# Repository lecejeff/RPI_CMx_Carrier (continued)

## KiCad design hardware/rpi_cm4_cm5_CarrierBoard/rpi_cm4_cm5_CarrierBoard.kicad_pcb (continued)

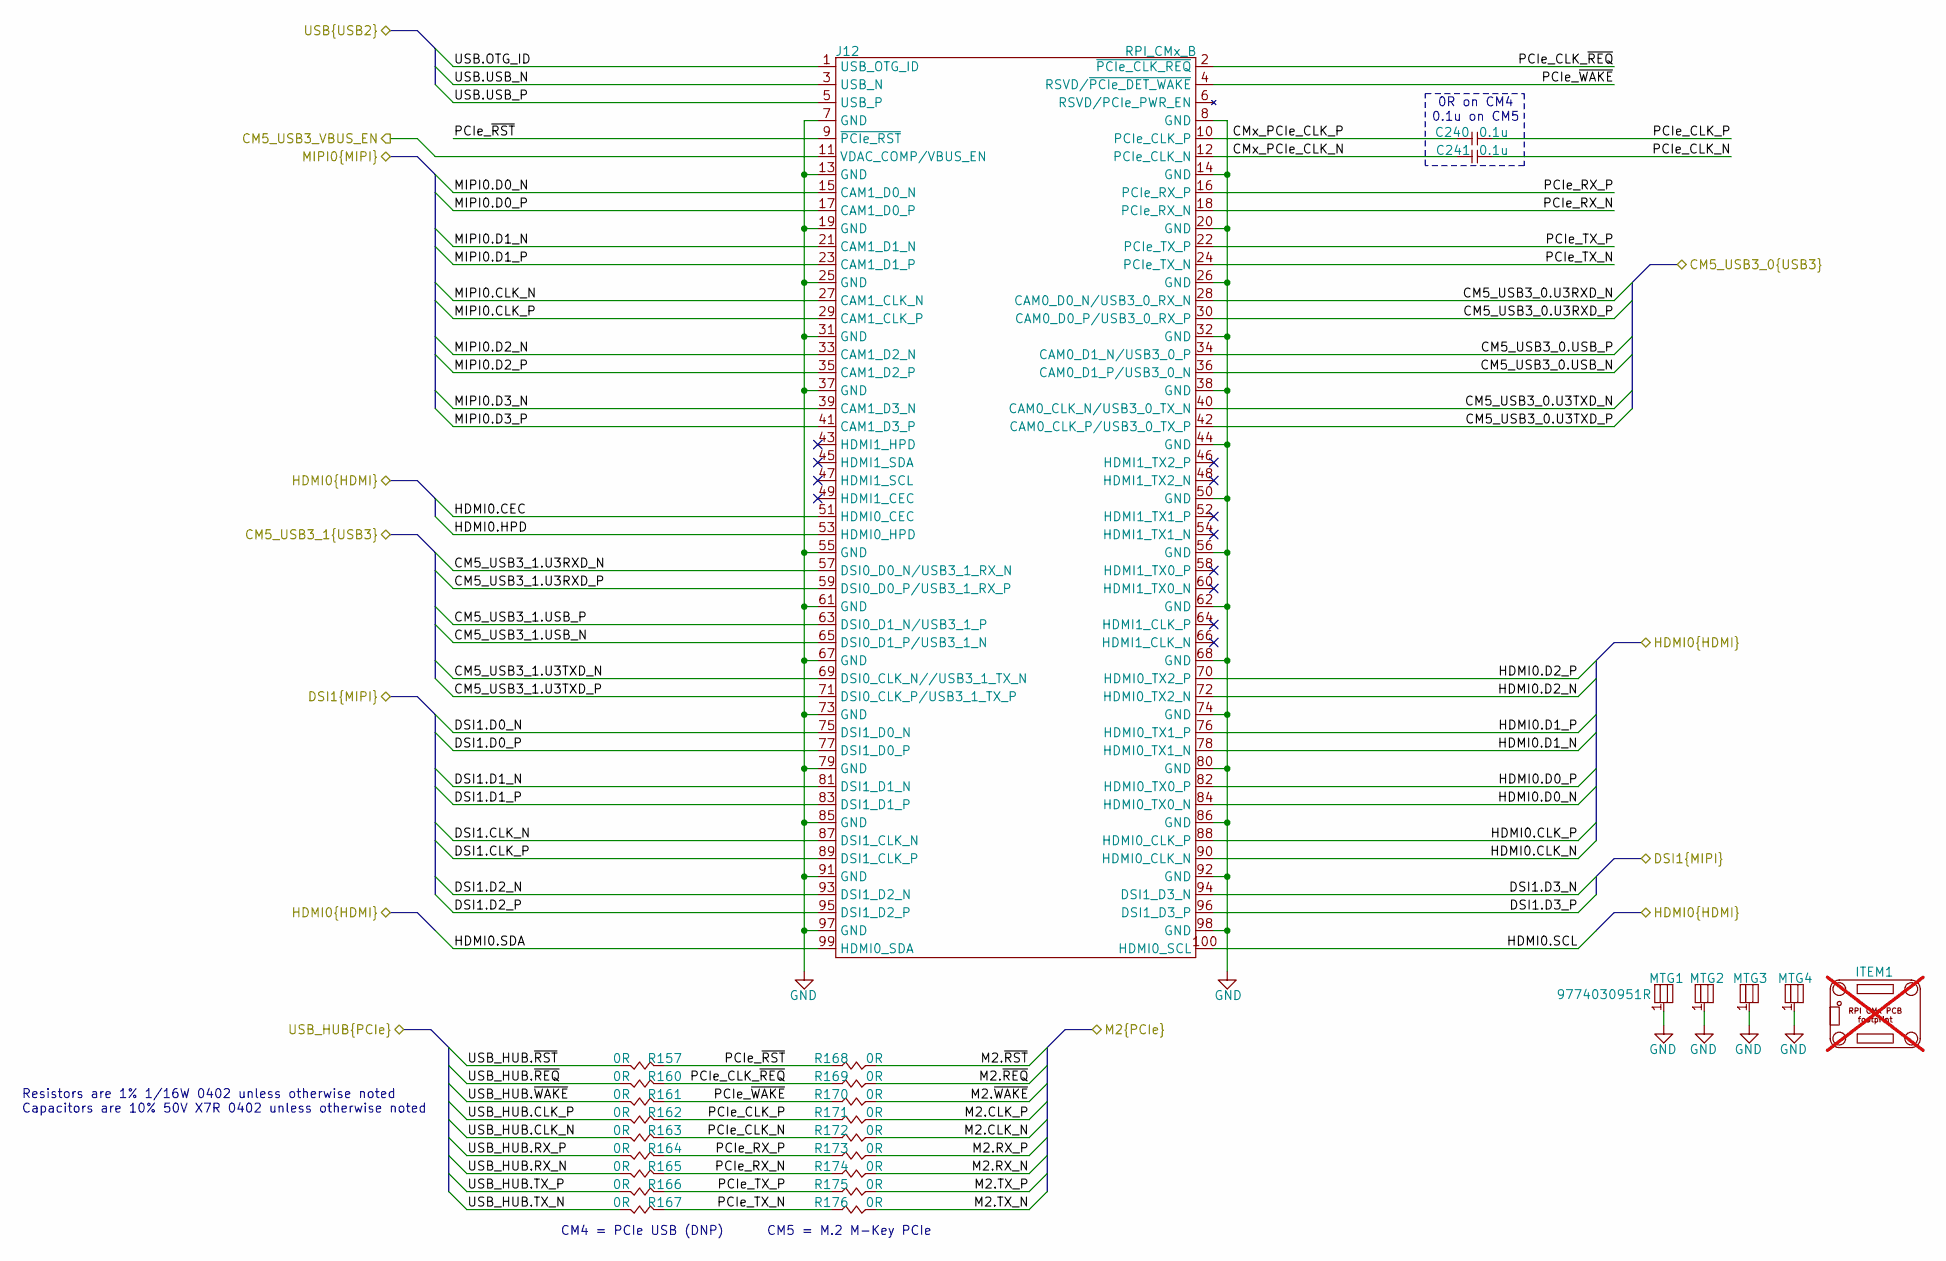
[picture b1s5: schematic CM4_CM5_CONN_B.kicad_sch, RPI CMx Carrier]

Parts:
C240, C241: 0.1u; CAP_NONPOL_0402; Tolerance ±10%; Voltage Rating 50V; Manufacturer Part Number GRM155R71H104KE14D
ITEM1: Raspberry PI CM4 and CM5 symbol; rPI_CM4_CM5; not fitted
J12: RPI_CMx_B; DF40HC(3.0)-100DS-0.4V; Current Rating 0.5A; Voltage Rating 150V; Manufacturer Part Number DF40HC(3.0)-100DS-0.4V(58)
MTG1, MTG2, MTG3, MTG4: 9774030951R; 9774030151R; Manufacturer Part Number 9774030951R
R157, R160, R161, R162, R163, R164, R165, R166, R167, R168, R169, R170, R171, R172, R173, R174, R175, R176: 0R; RES_0402; Tolerance 1%; Manufacturer Part Number RC0402FR-071KL

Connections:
/CM4_CM5_CONN_B/CMx_PCIe_CLK_N: C241.1, J12.12 (PCIe_CLK_N)
/CM4_CM5_CONN_B/CMx_PCIe_CLK_P: C240.1, J12.10 (PCIe_CLK_P)
/CM4_CM5_CONN_B/PCIe_CLK_N: C241.2, R163.1, R172.1
/CM4_CM5_CONN_B/PCIe_CLK_P: C240.2, R162.1, R171.1
/CM4_CM5_CONN_B/PCIe_CLK_~REQ: J12.2 (~PCIe_CLK_REQ), R160.1, R169.1
/CM4_CM5_CONN_B/PCIe_RX_N: J12.18 (PCIe_RX_N), R165.1, R174.1
/CM4_CM5_CONN_B/PCIe_RX_P: J12.16 (PCIe_RX_P), R164.1, R173.1
/CM4_CM5_CONN_B/PCIe_TX_N: J12.24 (PCIe_TX_N), R167.1, R176.1
/CM4_CM5_CONN_B/PCIe_TX_P: J12.22 (PCIe_TX_P), R166.1, R175.1
/CM4_CM5_CONN_B/PCIe_~RST: J12.9 (~PCIe_RST), R157.1, R168.1
/CM4_CM5_CONN_B/PCIe_~WAKE: J12.4 (RSVD/~PCIe_DET_WAKE), R161.1, R170.1
/CM5_USB3_0.U3RXD_N: J12.28 (CAM0_D0_N/USB3_0_RX_N); also elsewhere on the board
/CM5_USB3_0.U3RXD_P: J12.30 (CAM0_D0_P/USB3_0_RX_P); also elsewhere on the board
/CM5_USB3_0.U3TXD_N: J12.40 (CAM0_CLK_N/USB3_0_TX_N); also elsewhere on the board
/CM5_USB3_0.U3TXD_P: J12.42 (CAM0_CLK_P/USB3_0_TX_P); also elsewhere on the board
/CM5_USB3_0.USB_N: J12.36 (CAM0_D1_P/USB3_0_N); also elsewhere on the board
/CM5_USB3_0.USB_P: J12.34 (CAM0_D1_N/USB3_0_P); also elsewhere on the board
/CM5_USB3_1.U3RXD_N: J12.57 (DSI0_D0_N/USB3_1_RX_N); also elsewhere on the board
/CM5_USB3_1.U3RXD_P: J12.59 (DSI0_D0_P/USB3_1_RX_P); also elsewhere on the board
/CM5_USB3_1.U3TXD_N: J12.69 (DSI0_CLK_N//USB3_1_TX_N); also elsewhere on the board
/CM5_USB3_1.U3TXD_P: J12.71 (DSI0_CLK_P/USB3_1_TX_P); also elsewhere on the board
/CM5_USB3_1.USB_N: J12.65 (DSI0_D1_P/USB3_1_N); also elsewhere on the board
/CM5_USB3_1.USB_P: J12.63 (DSI0_D1_N/USB3_1_P); also elsewhere on the board
/DSI1.CLK_N: J12.87 (DSI1_CLK_N); also elsewhere on the board
/DSI1.CLK_P: J12.89 (DSI1_CLK_P); also elsewhere on the board
/DSI1.D0_N: J12.75 (DSI1_D0_N); also elsewhere on the board
/DSI1.D0_P: J12.77 (DSI1_D0_P); also elsewhere on the board
/DSI1.D1_N: J12.81 (DSI1_D1_N); also elsewhere on the board
/DSI1.D1_P: J12.83 (DSI1_D1_P); also elsewhere on the board
/DSI1.D2_N: J12.93 (DSI1_D2_N); also elsewhere on the board
/DSI1.D2_P: J12.95 (DSI1_D2_P); also elsewhere on the board
/DSI1.D3_N: J12.94 (DSI1_D3_N); also elsewhere on the board
/DSI1.D3_P: J12.96 (DSI1_D3_P); also elsewhere on the board
/HDMI0.CEC: J12.51 (HDMI0_CEC); also elsewhere on the board
/HDMI0.CLK_N: J12.90 (HDMI0_CLK_N); also elsewhere on the board
/HDMI0.CLK_P: J12.88 (HDMI0_CLK_P); also elsewhere on the board
/HDMI0.D0_N: J12.84 (HDMI0_TX0_N); also elsewhere on the board
/HDMI0.D0_P: J12.82 (HDMI0_TX0_P); also elsewhere on the board
/HDMI0.D1_N: J12.78 (HDMI0_TX1_N); also elsewhere on the board
/HDMI0.D1_P: J12.76 (HDMI0_TX1_P); also elsewhere on the board
/HDMI0.D2_N: J12.72 (HDMI0_TX2_N); also elsewhere on the board
/HDMI0.D2_P: J12.70 (HDMI0_TX2_P); also elsewhere on the board
/HDMI0.HPD: J12.53 (HDMI0_HPD); also elsewhere on the board
/HDMI0.SCL: J12.100 (HDMI0_SCL); also elsewhere on the board
/HDMI0.SDA: J12.99 (HDMI0_SDA); also elsewhere on the board
/M2.CLK_N: R172.2; also elsewhere on the board
/M2.CLK_P: R171.2; also elsewhere on the board
/M2.RX_N: R174.2; also elsewhere on the board
/M2.RX_P: R173.2; also elsewhere on the board
/M2.TX_N: R176.2; also elsewhere on the board
/M2.TX_P: R175.2; also elsewhere on the board
/M2.~REQ: R169.2; also elsewhere on the board
/M2.~RST: R168.2; also elsewhere on the board
/M2.~WAKE: R170.2; also elsewhere on the board
/MIPI0.CLK_N: J12.27 (CAM1_CLK_N); also elsewhere on the board
/MIPI0.CLK_P: J12.29 (CAM1_CLK_P); also elsewhere on the board
/MIPI0.D0_N: J12.15 (CAM1_D0_N); also elsewhere on the board
/MIPI0.D0_P: J12.17 (CAM1_D0_P); also elsewhere on the board
/MIPI0.D1_N: J12.21 (CAM1_D1_N); also elsewhere on the board
/MIPI0.D1_P: J12.23 (CAM1_D1_P); also elsewhere on the board
/MIPI0.D2_N: J12.33 (CAM1_D2_N); also elsewhere on the board
/MIPI0.D2_P: J12.35 (CAM1_D2_P); also elsewhere on the board
/MIPI0.D3_N: J12.39 (CAM1_D3_N); also elsewhere on the board
/MIPI0.D3_P: J12.41 (CAM1_D3_P); also elsewhere on the board
/USB.OTG_ID: J12.1 (USB_OTG_ID); also elsewhere on the board
/USB.USB_N: J12.3 (USB_N); also elsewhere on the board
/USB.USB_P: J12.5 (USB_P); also elsewhere on the board
/USB_3/CM5_USB3_VBUS_EN: J12.11 (VDAC_COMP/VBUS_EN); also elsewhere on the board
/USB_HUB.CLK_N: R163.2; also elsewhere on the board
/USB_HUB.CLK_P: R162.2; also elsewhere on the board
/USB_HUB.RX_N: R165.2; also elsewhere on the board
/USB_HUB.RX_P: R164.2; also elsewhere on the board
/USB_HUB.TX_N: R167.2; also elsewhere on the board
/USB_HUB.TX_P: R166.2; also elsewhere on the board
/USB_HUB.~REQ: R160.2; also elsewhere on the board
/USB_HUB.~RST: R157.2; also elsewhere on the board
/USB_HUB.~WAKE: R161.2; also elsewhere on the board
GND: J12.7 (GND), J12.8 (GND), J12.13 (GND), J12.14 (GND), J12.19 (GND), J12.20 (GND), J12.25 (GND), J12.26 (GND), J12.31 (GND), J12.32 (GND), J12.37 (GND), J12.38 (GND), J12.44 (GND), J12.50 (GND), J12.55 (GND), J12.56 (GND), J12.61 (GND), J12.62 (GND), J12.67 (GND), J12.68 (GND), J12.73 (GND), J12.74 (GND), J12.79 (GND), J12.80 (GND), J12.85 (GND), J12.86 (GND), J12.91 (GND), J12.92 (GND), J12.97 (GND), J12.98 (GND), MTG1.1, MTG2.1, MTG3.1, MTG4.1; also elsewhere on the board

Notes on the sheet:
Resistors are 1% 1/16W 0402 unless otherwise noted Capacitors are 10% 50V X7R 0402 unless otherwise noted
0R on CM4 0.1u on CM5
CM4 = PCIe USB (DNP)
CM5 = M.2 M-Key PCIe

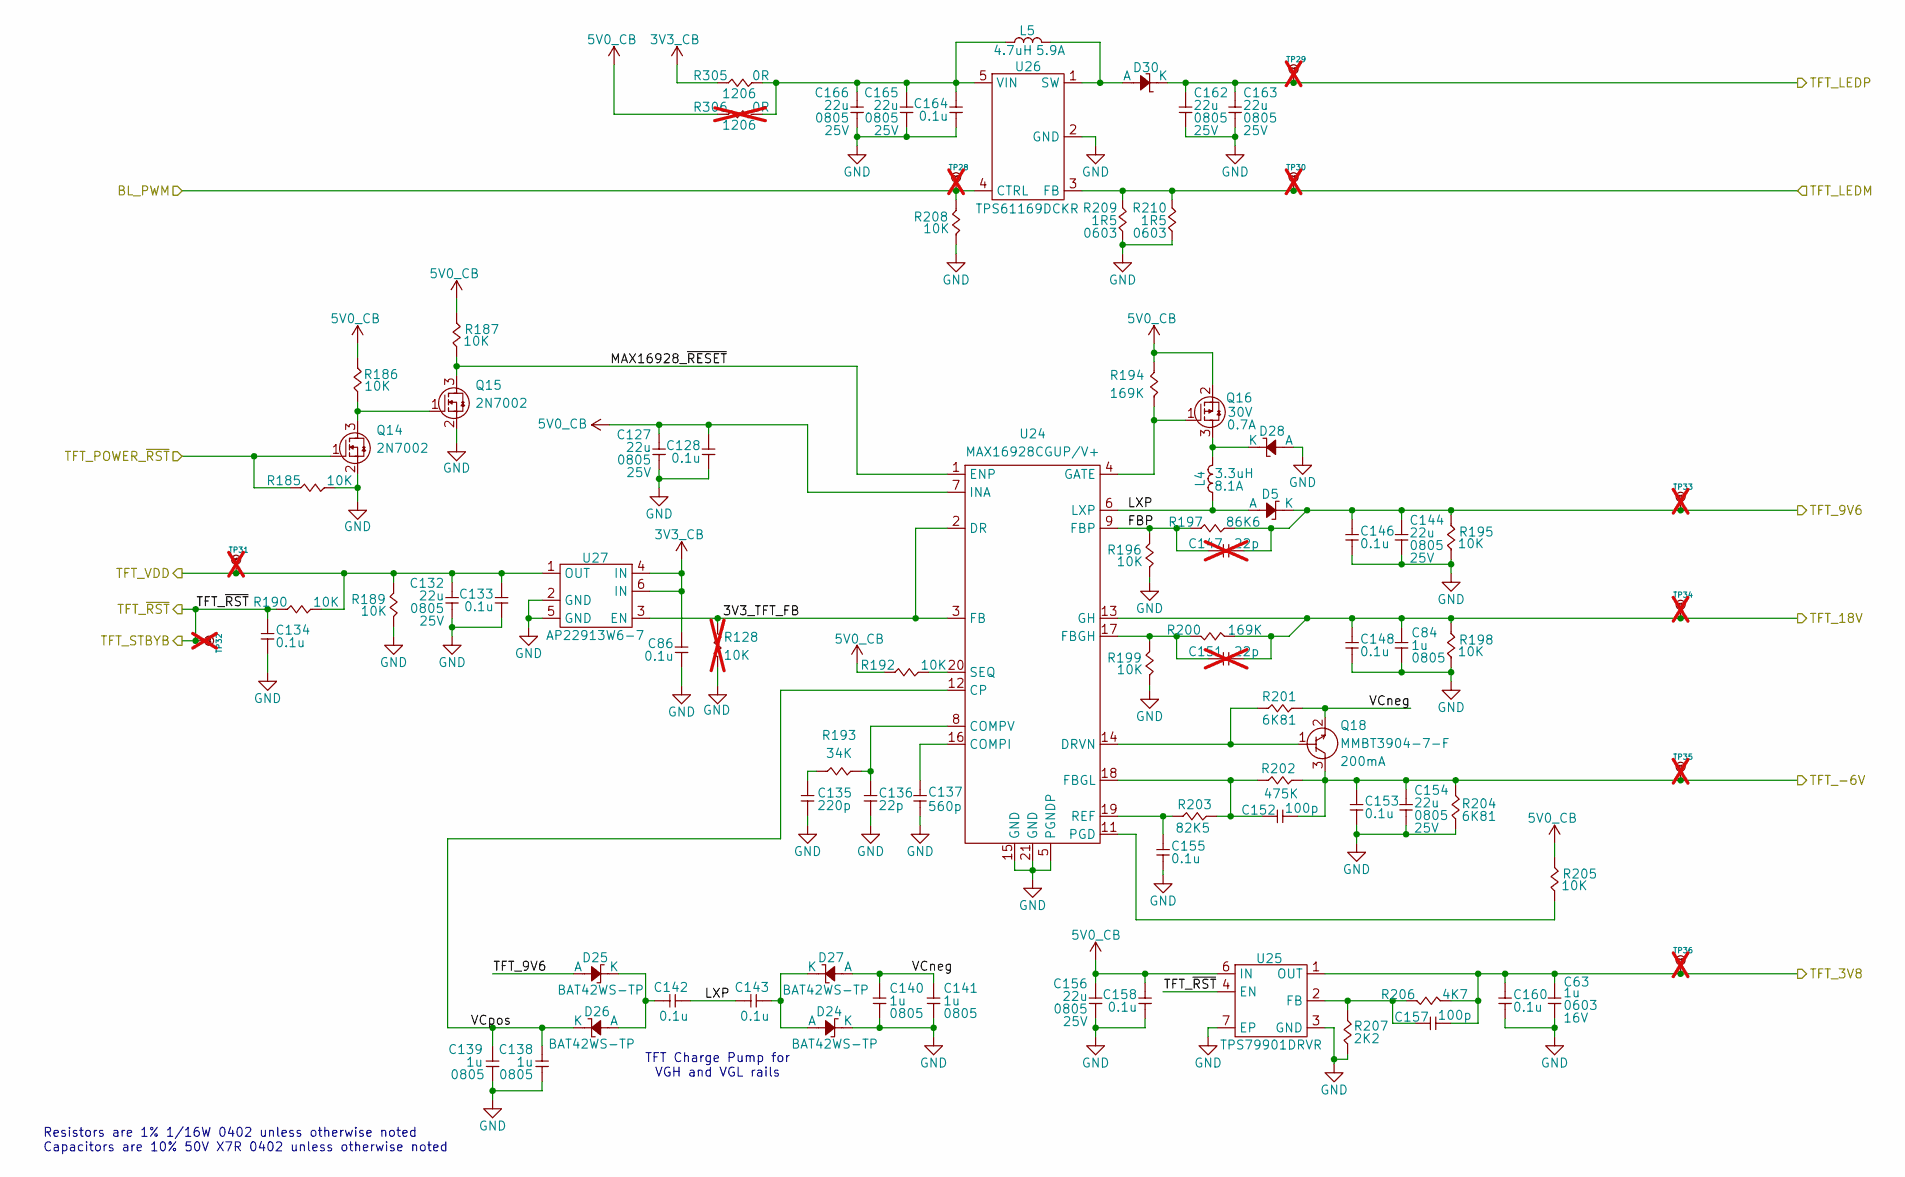
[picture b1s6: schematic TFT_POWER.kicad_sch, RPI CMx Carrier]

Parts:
C63: 1u; CAP_NONPOL_0603; Tolerance ±10%; Voltage Rating 16V; Manufacturer Part Number CC0603KRX7R7BB105
C84, C138, C139, C140, C141: 1u; CAP_NONPOL_0805; Tolerance ±10%; Voltage Rating 50V; Manufacturer Part Number CC0805KKX7R9BB105
C86, C128, C133, C134, C142, C143, C146, C148, C153, C155, C158, C160, C164: 0.1u; CAP_NONPOL_0402; Tolerance ±10%; Voltage Rating 50V; Manufacturer Part Number GRM155R71H104KE14D
C127, C132, C144, C154, C156, C162, C163, C165, C166: 22u; CAP_NONPOL_0805; Tolerance ±20%; Voltage Rating 25V; Manufacturer Part Number CL21A226MAYNNNE
C135: 220p; CAP_NONPOL_0402; Tolerance ±5%; Voltage Rating 50V; Manufacturer Part Number CL05C221JB5NNNC
C136: 22p; CAP_NONPOL_0402; Tolerance ±10%; Voltage Rating 50V; Manufacturer Part Number C0402C220K5GACTU
C137: 560p; CAP_NONPOL_0402; Tolerance ±5%; Voltage Rating 50V; Manufacturer Part Number GRM1555C1H561JA01D
C147, C151: 22p; CAP_NONPOL_0402; Tolerance ±10%; Voltage Rating 50V; Manufacturer Part Number C0402C220K5GACTU; not fitted
C152, C157: 100p; CAP_NONPOL_0402; Tolerance ±5%; Voltage Rating 50V; Manufacturer Part Number CC0402JRNPO9BN101
D5, D24, D25, D26, D27, D28: BAT42WS-TP; SOD-323; Tolerance NA; Manufacturer Part Number BAT42WS-TP
D30: SK34A-LTP; DO-214AC; Tolerance NA; Manufacturer Part Number SK34A-LTP
L4: PA5003.332NLT; PA5003; Tolerance ±20%; Manufacturer Part Number PA5003.332NLT
L5: PA5003.472NLT; PA5003; Tolerance ±20%; Manufacturer Part Number PA5003.472NLT
Q14, Q15: 2N7002; SOT-23-3; Manufacturer Part Number 2N7002-7-F
Q16: DMP3030SN-7; SOT-23-3; Manufacturer Part Number DMP3030SN-7
Q18: MMBT3904-7-F; SOT-23-3; Manufacturer Part Number MMBT3904-7-F
R128: 10K; RES_0402; Tolerance 1%; Manufacturer Part Number RC0402FR-0710KL; not fitted
R185, R186, R187, R189, R190, R192, R195, R196, R198, R199, R205, R208: 10K; RES_0402; Tolerance 1%; Manufacturer Part Number RC0402FR-0710KL
R193: 34K; RES_0402; Tolerance 1%; Manufacturer Part Number RC0402FR-1334KL
R194, R200: 169K; RES_0402; Tolerance 1%; Manufacturer Part Number RC0402FR-07169KL
R197: 86K6; RES_0402; Tolerance 1%; Manufacturer Part Number AC0402FR-0786K6L
R201, R204: 6K81; RES_0402; Tolerance 1%; Manufacturer Part Number RC0402FR-076K81L
R202: 475K; RES_0402; Tolerance 1%; Manufacturer Part Number RC0402FR-07475KL
R203: 82K5; RES_0402; Tolerance 1%; Manufacturer Part Number RC0402FR-0782K5L
R206: 4K7; RES_0402; Tolerance 1%; Manufacturer Part Number RC0402FR-074K7L
R207: 2K2; RES_0402; Tolerance 1%; Manufacturer Part Number RC0402FR-072K2P
R209, R210: 1R5; RES_0603; Tolerance 1%; Manufacturer Part Number RC0603FR-131R5L
R305: 0R; RES_1206; Tolerance 1%; Manufacturer Part Number RC1206JR-070RL
R306: 0R; RES_1206; Tolerance 1%; Manufacturer Part Number RC1206JR-070RL; not fitted
TP28, TP29, TP30, TP31, TP32, TP33, TP34, TP35, TP36: 28 mils; SMT_TP_28_MILS; Manufacturer Part Number NA; not fitted
U24: MAX16928CGUP/V+; TSSOP-20-EP; Input Voltage (Min) 3V; Input Voltage (Max) 5.5V; Manufacturer Part Number MAX16928CGUP/V+
U25: TPS79901DRVR; WSON-6-EP; Input Voltage (Min) 2.7V; Input Voltage (Max) 6.5V; Manufacturer Part Number TPS79901DRVR
U26: TPS61169DCKR; SC-70-5; Input Voltage (Min) 2.7V; Input Voltage (Max) 5.5V; Manufacturer Part Number TPS61169DCKR
U27: AP22913W6-7; SOT-23-6; Load Voltage 1.5V ~ 5.5V; Manufacturer Part Number AP22913W6-7

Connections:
3V3_CB: C86.2, R305.1, U27.4 (IN), U27.6 (IN); also elsewhere on the board
5V0_CB: C127.2, C128.2, C156.2, C158.2, Q16.2 (S), R186.2, R187.2, R192.2, R194.2, R205.2, R306.1, U24.7 (INA), U25.6 (IN); also elsewhere on the board
/CM4_CM5_CONN_A/PWM_0: R208.2, TP28.1, U26.4 (CTRL); also elsewhere on the board
/TFT_CONN/TFT_LEDM: R209.2, R210.2, TP30.1, U26.3 (FB); also elsewhere on the board
/TFT_CONN/TFT_LEDP: C162.2, C163.2, D30.1 (K), TP29.1; also elsewhere on the board
/TFT_CONN/TFT_VCOM: C63.2, C157.2, C160.2, R206.1, TP36.1, U25.1 (OUT); also elsewhere on the board
/TFT_CONN/TFT_VDD: C132.2, C133.2, R189.2, R190.1, TP31.1, U27.1 (OUT); also elsewhere on the board
/TFT_CONN/TFT_VGH: C84.2, C148.2, C151.1, R198.2, R200.1, TP34.1, U24.13 (GH); also elsewhere on the board
/TFT_CONN/TFT_VGL: C152.2, C153.2, C154.2, Q18.3 (C), R202.2, R204.2, TP35.1; also elsewhere on the board
/TFT_POWER/3V3_TFT_FB: R128.2, U24.2 (DR), U24.3 (FB), U27.3 (EN)
/TFT_POWER/FBP: C147.2, R196.2, R197.1, U24.9 (FBP)
/TFT_POWER/LXP: C142.1, C143.2, D5.2 (A), L4.1, U24.6 (LXP)
/TFT_POWER/MAX16928_~RESET: Q15.3 (D), R187.1, U24.1 (ENP)
/TFT_POWER/TFT_9V6: C144.2, C146.2, C147.1, D5.1 (K), D25.2 (A), R195.2, R197.2, TP33.1; also elsewhere on the board
/TFT_POWER/TFT_~RST: C134.2, R190.2, TP32.1, U25.4 (EN); also elsewhere on the board
/TFT_POWER/VCneg: C140.2, C141.2, D27.2 (A), Q18.2 (E), R201.2
/TFT_POWER/VCpos: C138.2, C139.2, D26.1 (K), U24.12 (CP)
/TFT_POWER_~RST: Q14.1 (G), R185.2; also elsewhere on the board
GND: C63.1, C84.1, C86.1, C127.1, C128.1, C132.1, C133.1, C134.1, C135.1, C136.1, C137.1, C138.1, C139.1, C140.1, C141.1, C144.1, C146.1, C148.1, C153.1, C154.1, C155.1, C156.1, C158.1, C160.1, C162.1, C163.1, C164.1, C165.1, C166.1, D24.1 (K), D28.2 (A), Q14.2 (S), Q15.2 (S), R128.1, R185.1, R189.1, R195.1, R196.1, R198.1, R199.1, R204.1, R207.1, R208.1, R209.1, R210.1, U24.5 (PGNDP), U24.15 (GND), U24.21 (GND), U25.3 (GND), U25.7 (EP), U26.2 (GND), U27.2 (GND), U27.5 (GND); also elsewhere on the board
unnamed: C135.2, R193.1
unnamed: C143.1, D24.2 (A), D27.1 (K)
unnamed: C142.2, D25.1 (K), D26.2 (A)
unnamed: D28.1 (K), L4.2, Q16.3 (D)
unnamed: D30.2 (A), L5.2, U26.1 (SW)
unnamed: Q14.3 (D), Q15.1 (G), R186.1
unnamed: Q16.1 (G), R194.1, U24.4 (GATE)
unnamed: Q18.1 (B), R201.1, U24.14 (DRVN)
unnamed: C137.2, U24.16 (COMPI)
unnamed: C136.2, R193.2, U24.8 (COMPV)
unnamed: C151.2, R199.2, R200.2, U24.17 (FBGH)
unnamed: C152.1, R202.1, R203.2, U24.18 (FBGL)
unnamed: R205.1, U24.11 (PGD)
unnamed: C155.2, R203.1, U24.19 (REF)
unnamed: R192.1, U24.20 (SEQ)
unnamed: C157.1, R206.2, R207.2, U25.2 (FB)
unnamed: C164.2, C165.2, C166.2, L5.1, R305.2, R306.2, U26.5 (VIN)

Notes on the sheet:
Resistors are 1% 1/16W 0402 unless otherwise noted Capacitors are 10% 50V X7R 0402 unless otherwise noted
TFT Charge Pump for VGH and VGL rails

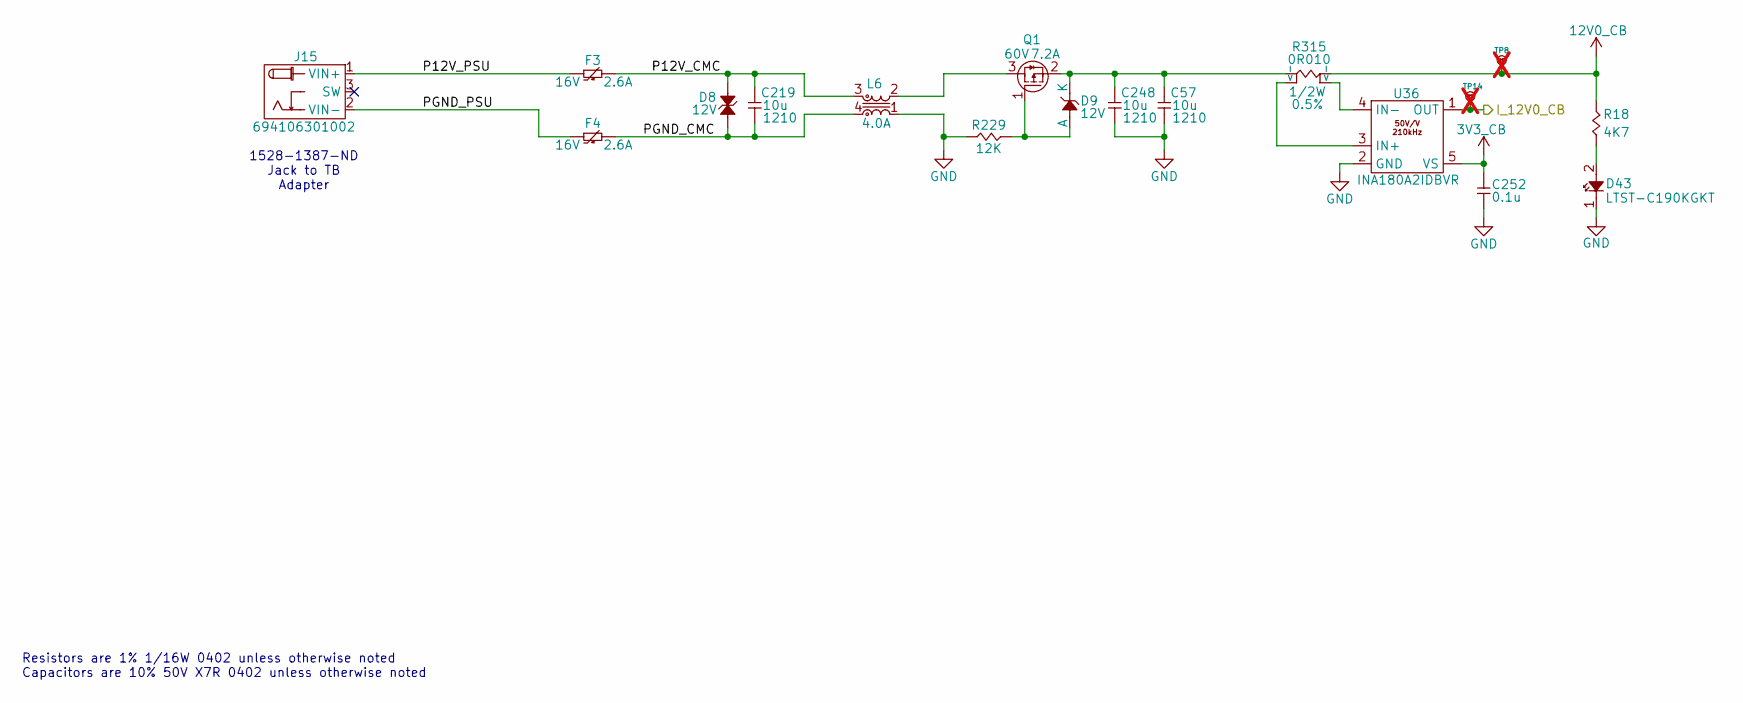
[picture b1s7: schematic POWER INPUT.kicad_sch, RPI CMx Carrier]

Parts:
C57, C219, C248: 10u; CAP_NONPOL_1210; Tolerance ±10%; Voltage Rating 50V; Manufacturer Part Number C3225X7R1H106K250AC
C252: 0.1u; CAP_NONPOL_0402; Tolerance ±10%; Voltage Rating 50V; Manufacturer Part Number GRM155R71H104KE14D
D8: SMAJ12CA; DO-214AC; Manufacturer Part Number SMAJ12CA
D9: MMSZ5242B-TP; SOD-123; Tolerance ±5%; Manufacturer Part Number MMSZ5242B-TP
D43: LTST-C190KGKT; LED_0603; Tolerance NA; Manufacturer Part Number LTST-C190KGKT
F3, F4: MINISMDC260F/16-2; PTC_1812; Voltage 16V; Manufacturer Part Number MINISMDC260F/16-2
J15: 694106301002; Current Rating 5A; Voltage Rating 24V; Manufacturer Part Number 694106301002
L6: CM7060P701R-10; CM7060; Tolerance NA; Manufacturer Part Number CM7060P701R-10
Q1: DMPH6050SK3-13; TO-252-3; Manufacturer Part Number DMPH6050SK3-13
R18: 4K7; RES_0402; Tolerance 1%; Manufacturer Part Number RC0402FR-074K7L
R229: 12K; RES_0402; Tolerance 1%; Manufacturer Part Number RC0402FR-1312KL
R315: 0R010; RES_SENSE_1206; Tolerance 0.5%; Manufacturer Part Number LVK12R010DER
TP8, TP14: 28 mils; SMT_TP_28_MILS; Manufacturer Part Number NA; not fitted
U36: INA180A2IDBVR; SOT-23-5; Offset Voltage 100uV; Supply Voltage 2.7V ~ 5.5V; Manufacturer Part Number INA180A2IDBVR

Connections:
3V3_CB: C252.2, U36.5 (VS); also elsewhere on the board
12V0_CB: R18.2, R315.4 (I), TP8.1; also elsewhere on the board
/PIC32AK1216/I_12V0_CB: TP14.1, U36.1 (OUT); also elsewhere on the board
/POWER INPUT/P12V_CMC: C219.2, D8.2, F3.2, L6.3
/POWER INPUT/P12V_PSU: F3.1, J15.1 (VIN+)
/POWER INPUT/PGND_CMC: C219.1, D8.1, F4.2, L6.4
/POWER INPUT/PGND_PSU: F4.1, J15.2 (VIN-)
GND: C57.1, C248.1, C252.1, D43.1 (K), L6.1, R229.1, U36.2 (GND); also elsewhere on the board
unnamed: D9.2 (A), Q1.1 (G), R229.2
unnamed: C57.2, C248.2, D9.1 (K), Q1.2 (S), R315.1 (I)
unnamed: D43.2 (A), R18.1
unnamed: L6.2, Q1.3 (D)
unnamed: R315.2 (V), U36.3 (IN+)
unnamed: R315.3 (V), U36.4 (IN-)

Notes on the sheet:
1528-1387-ND Jack to TB Adapter
Resistors are 1% 1/16W 0402 unless otherwise noted Capacitors are 10% 50V X7R 0402 unless otherwise noted

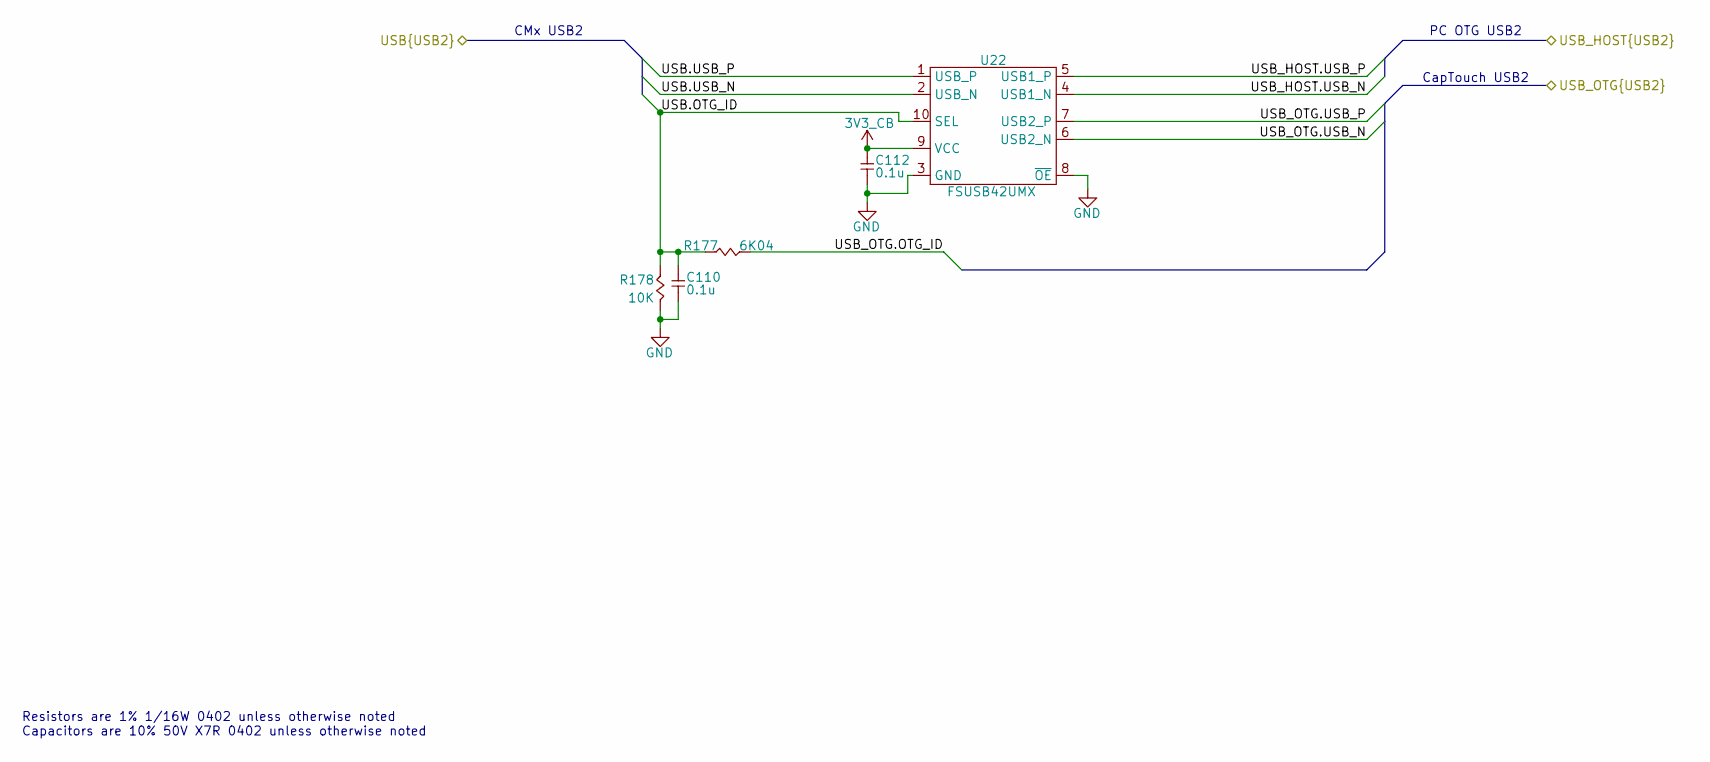
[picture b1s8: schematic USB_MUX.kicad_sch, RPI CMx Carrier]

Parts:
C110, C112: 0.1u; CAP_NONPOL_0402; Tolerance ±10%; Voltage Rating 50V; Manufacturer Part Number GRM155R71H104KE14D
R177: 6K04; RES_0402; Tolerance 1%; Manufacturer Part Number RC0402FR-076K04P
R178: 10K; RES_0402; Tolerance 1%; Manufacturer Part Number RC0402FR-0710KL
U22: FSUSB42UMX; 10-UMLP; Supply Voltage 2.4V ~ 4.4V; Manufacturer Part Number FSUSB42UMX

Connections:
3V3_CB: C112.2, U22.9 (VCC); also elsewhere on the board
/TFT_CONN/USB_HOST.USB_N: U22.4 (USB1_N); also elsewhere on the board
/TFT_CONN/USB_HOST.USB_P: U22.5 (USB1_P); also elsewhere on the board
/USB.OTG_ID: C110.2, R177.1, R178.2, U22.10 (SEL); also elsewhere on the board
/USB.USB_N: U22.2 (USB_N); also elsewhere on the board
/USB.USB_P: U22.1 (USB_P); also elsewhere on the board
/USB_OTG.OTG_ID: R177.2; also elsewhere on the board
/USB_OTG.USB_N: U22.6 (USB2_N); also elsewhere on the board
/USB_OTG.USB_P: U22.7 (USB2_P); also elsewhere on the board
GND: C110.1, C112.1, R178.1, U22.3 (GND), U22.8 (~OE); also elsewhere on the board

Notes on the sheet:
CapTouch USB2
Resistors are 1% 1/16W 0402 unless otherwise noted Capacitors are 10% 50V X7R 0402 unless otherwise noted
CMx USB2
PC OTG USB2

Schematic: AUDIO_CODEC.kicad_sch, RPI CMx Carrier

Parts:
C203, C204, C208, C211, C212, C214, C217: 0.1u; CAP_NONPOL_0402; Tolerance ±10%; Voltage Rating 50V; Manufacturer Part Number GRM155R71H104KE14D
C205: 1u; CAP_NONPOL_0805; Tolerance ±10%; Voltage Rating 50V; Manufacturer Part Number CC0805KKX7R9BB105; not fitted
C206, C207, C209, C210, C213, C215: 1u; CAP_NONPOL_0805; Tolerance ±10%; Voltage Rating 50V; Manufacturer Part Number CC0805KKX7R9BB105
C216: 10u; CAP_NONPOL_0805; Tolerance ±10%; Voltage Rating 16V; Manufacturer Part Number CL21A106KOQNNNE
D44, D45: D1213A-02SOL-7; SOT-23-3; Manufacturer Part Number D1213A-02SOL-7
J13, J14: SJ-3523-SMT-TR; SJ-352X-SMT; Current Rating 1A; Voltage Rating 12V; Manufacturer Part Number SJ-3523-SMT-TR
R16, R17, R279: 10K; RES_0402; Tolerance 1%; Manufacturer Part Number RC0402FR-0710KL
R275: 2K2; RES_0402; Tolerance 1%; Manufacturer Part Number RC0402FR-072K2P; not fitted
R276, R277: 22R; RES_0402; Tolerance 1%; Manufacturer Part Number RC0402FR-0722RL
TP37, TP38, TP39, TP40: 28 mils; SMT_TP_28_MILS; Manufacturer Part Number NA; not fitted
U2: ECS-2016MVQ-120-BP-TR; 4-SMD_2mmx1_6mm; Tolerance ±50ppm; Supply Voltage 3.3V; Manufacturer Part Number ECS-2016MVQ-120-BP-TR
U33: SGTL5000XNBA3R2; 32-HPQFN; Supply Voltage 1.1V ~ 3.6V; Manufacturer Part Number SGTL5000XNBA3R2
X1: CMM-3729AT-42308-TR; Manufacturer Part Number CMM-3729AT-42308-TR

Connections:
1V8_CB: C211.2, C213.2, U33.30 (VDDD); also elsewhere on the board
3V3_CB: C203.2, C212.2, C214.2, C215.2, C216.2, C217.2, U2.4 (VDD), U33.5 (VDDA), U33.20 (VDDIO), X1.1 (VDD); also elsewhere on the board
/AUDIO_CODEC/CODEC_CLK_12MHz: R277.2, U33.21 (MCLK)
/AUDIO_CODEC/HEADPHONE_L: D45.1, J14.2 (L), U33.6 (HP_L)
/AUDIO_CODEC/HEADPHONE_R: D45.2 (A), J14.3 (R), U33.2 (HP_R)
/AUDIO_CODEC/HEADPHONE_VGND: D45.3 (GND), J14.1 (SLV), U33.4 (HP_VGND)
/AUDIO_CODEC/LINE_IN_L: C206.2, R17.2
/AUDIO_CODEC/LINE_IN_R: C207.2, R16.2
/AUDIO_CODEC/LINE_OUT_L: C209.1, D44.2 (A), J13.2 (L)
/AUDIO_CODEC/LINE_OUT_R: C210.1, D44.1, J13.3 (R)
/AUDIO_CODEC/MIC_IN: C204.1, U33.15 (MIC)
/CODEC_~RST: R279.2, U2.1 (EN); also elsewhere on the board
/I2C3.I2C_SCL: U33.29 (CTRL_CLK); also elsewhere on the board
/I2C3.I2C_SDA: U33.27 (CTRL_DATA); also elsewhere on the board
/I2S_COFS: TP39.1, U33.23 (LRCLK); also elsewhere on the board
/I2S_DIN: R276.2, TP38.1; also elsewhere on the board
/I2S_DOUT: TP37.1, U33.26 (DIN); also elsewhere on the board
/I2S_SCLK: TP40.1, U33.24 (SCLK); also elsewhere on the board
GND: C203.1, C205.2, C208.1, C211.1, C212.1, C213.1, C214.1, C215.1, C216.1, C217.1, D44.3 (GND), J13.1 (SLV), R16.1, R17.1, R279.1, U2.2 (GND), U33.1 (GND), U33.3 (GND), U33.7 (AGND), U33.31 (CTRL_ADR0_CS), U33.32 (MODE), U33.33 (GND), X1.2 (GND), X1.3 (GND); also elsewhere on the board
unnamed: R277.1, U2.3 (OUT)
unnamed: R276.1, U33.25 (DOUT)
unnamed: C206.1, U33.14 (LINE_IN_L)
unnamed: C207.1, U33.13 (LINE_IN_R)
unnamed: C209.2, U33.12 (LINE_OUT_L)
unnamed: C210.2, U33.11 (LINE_OUT_R)
unnamed: C205.1, R275.2, U33.16 (MIC_BIAS)
unnamed: C208.2, U33.10 (VAG)
unnamed: C204.2, R275.1, X1.4 (OUT)

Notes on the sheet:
Resistors are 1% 1/16W 0402 unless otherwise noted Capacitors are 10% 50V X7R 0402 unless otherwise noted
I2C3 PU Pop'd at DSI bridge

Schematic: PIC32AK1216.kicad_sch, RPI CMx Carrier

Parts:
C1, C42, C44, C46, C47, C50, C52, C53, C54, C55, C75, C85, C253: 0.1u; CAP_NONPOL_0402; Tolerance ±10%; Voltage Rating 50V; Manufacturer Part Number GRM155R71H104KE14D
C3, C4, C6, C45, C51: 1n; CAP_NONPOL_0402; Tolerance ±5%; Voltage Rating 50V; Manufacturer Part Number GRM1555C1H102JA01D
C5, C43: 22u; CAP_NONPOL_0805; Tolerance ±20%; Voltage Rating 25V; Manufacturer Part Number CL21A226MAYNNNE
C48, C49: 13p; CAP_NONPOL_0402; Tolerance ±2%; Voltage Rating 50V; Manufacturer Part Number GJM1555C1H130GB01D
C103: 1u; CAP_NONPOL_0805; Tolerance ±10%; Voltage Rating 50V; Manufacturer Part Number CC0805KKX7R9BB105
D1: ESD7016MUTAG; UDFN8; Manufacturer Part Number ESD7016MUTAG
D6, D7, D10: BAT42WS-TP; SOD-323; Tolerance NA; Manufacturer Part Number BAT42WS-TP
D49: D1213A-02SOL-7; SOT-23-3; Manufacturer Part Number D1213A-02SOL-7
J10: PR20206VBNN; HEADER_6P_2_54MM; Current Rating 3A; Voltage Rating 250V; Manufacturer Part Number PR20206VBNN
Q21, Q25, Q26: 2N7002; SOT-23-3; Manufacturer Part Number 2N7002-7-F
R1, R5, R6, R8, R22, R31, R62, R63, R65, R66, R69, R72, R74, R75, R76, R77, R78, R85, R87, R89, R114, R153, R179, R214, R232: 10K; RES_0402; Tolerance 1%; Manufacturer Part Number RC0402FR-0710KL
R3, R4, R23, R79, R80, R81, R82, R84, R86, R219, R220, R221, R222, R223, R226, R227, R228: 22R; RES_0402; Tolerance 1%; Manufacturer Part Number RC0402FR-0722RL
R7: 30K1; RES_0402; Tolerance 1%; Manufacturer Part Number RC0402FR-0730K1L
R24, R67, R70: 0R; RES_0402; Tolerance 1%; Manufacturer Part Number RC0402FR-071KL
R28: 0R; RES_0402; Tolerance 1%; Manufacturer Part Number RC0402FR-071KL; not fitted
R30, R73: 1Meg; RES_0402; Tolerance 1%; Manufacturer Part Number RC0402FR-131ML
R64: 100K; RES_0402; Tolerance 1%; Manufacturer Part Number RC0402FR-07100KL
R68, R71: 10K; RES_0402; Tolerance 1%; Manufacturer Part Number RC0402FR-0710KL; not fitted
R133: 1K; RES_0402; Tolerance 1%; Manufacturer Part Number RC0402FR-071KL
R216, R218: 4K7; RES_0402; Tolerance 1%; Manufacturer Part Number RC0402FR-074K7L
S1, S2: KSR233G LFG; Y35A23310FPLFG; Manufacturer Part Number KSR233G LFG
TP18, TP19, TP20, TP21, TP41, TP42, TP43, TP44: 28 mils; SMT_TP_28_MILS; Manufacturer Part Number NA; not fitted
U1: PIC32AK1216GC41064-I/M7; 64-VQFN-EP(9x9mm); Supply Voltage 3V ~ 3.6V; Manufacturer Part Number PIC32AK1216GC41064-I/M7
U20: STWD100NYWY3F; SOT-23-5; Supply Voltage 2.70V ~ 5.5V; Manufacturer Part Number STWD100NYWY3F
Y3: 20MHz; 4-SMD_2mmx1_6mm; Tolerance ±20ppm; Manufacturer Part Number ABM11-20.000MHZ-D2X-T3

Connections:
1V05_CB: R70.2; also elsewhere on the board
1V8_CB: R67.2; also elsewhere on the board
3V3_CB: C5.2, C43.2, C44.2, C47.2, C50.2, C52.2, C53.2, C54.2, C85.2, J10.2, R62.2, R63.2, R85.2, R89.2, R153.2, R179.2, R214.2, R216.2, R218.2, U1.5 (VDD), U1.11 (AVDD), U1.19 (VDD), U1.26 (VDD), U1.40 (VDD), U1.48 (VDD), U1.60 (VDD); also elsewhere on the board
5V0_CB: C75.2, D10.1 (K), R30.2, R31.2, R65.2, R232.2, U20.5 (VCC); also elsewhere on the board
12V0_CB: R7.2; also elsewhere on the board
/CM4_CM5_CONN_A/CM4_~CM5_BUILD: U1.52 (RD1); also elsewhere on the board
/CM4_CM5_CONN_A/CMx_INT: TP21.1, U1.50 (RD10); also elsewhere on the board
/CM4_CM5_CONN_A/PIC_INT: R114.2, U1.53 (RD2); also elsewhere on the board
/CM4_CM5_CONN_A/PPS_OUT: R86.2; also elsewhere on the board
/CM4_CM5_CONN_A/~WDOG_IN: TP20.1, U20.1 (~WDO); also elsewhere on the board
/I2C6.I2C_SCL: U1.57 (RD7); also elsewhere on the board
/I2C6.I2C_SDA: U1.58 (RD8); also elsewhere on the board
/MKB1.AN: U1.6 (RA11); also elsewhere on the board
/MKB1.INT: U1.51 (RD0); also elsewhere on the board
/MKB1.MISO: R87.2, U1.36 (RC7); also elsewhere on the board
/MKB1.MOSI: R220.2; also elsewhere on the board
/MKB1.PWM: R226.2; also elsewhere on the board
/MKB1.RX: R179.1, U1.44 (RC4); also elsewhere on the board
/MKB1.SCK: R4.2; also elsewhere on the board
/MKB1.SCL: R218.1, U1.55 (RD5); also elsewhere on the board
/MKB1.SDA: R216.1, U1.56 (RD6); also elsewhere on the board
/MKB1.TX: R219.2; also elsewhere on the board
/MKB1.~CS: U1.42 (RC5); also elsewhere on the board
/MKB1.~RST: R82.2; also elsewhere on the board
/PIC32AK1216/BTN1: D49.1, R62.1, R81.2, S1.2
/PIC32AK1216/I_1V8_CB: R5.2; also elsewhere on the board
/PIC32AK1216/I_3V3_CB: R6.2; also elsewhere on the board
/PIC32AK1216/I_5V0_CB: R1.2; also elsewhere on the board
/PIC32AK1216/I_12V0_CB: R69.2; also elsewhere on the board
/PIC32AK1216/LED1: U1.30 (RB7); also elsewhere on the board
/PIC32AK1216/LED2: U1.1 (RA0); also elsewhere on the board
/PIC32AK1216/PIC_DBG_RXD: R89.1, U1.45 (RC10); also elsewhere on the board
/PIC32AK1216/PIC_DBG_TXD: R228.2; also elsewhere on the board
/PIC32AK1216/POWER_KILL: R3.2, TP18.1; also elsewhere on the board
/PIC32AK1216/WDOG: Q25.1 (G), R84.2, TP19.1
/PIC32AK1216/WDOG_~EN: Q21.3 (D), R24.2, R31.1
/PIC_~RST: D6.1 (K); also elsewhere on the board
/SPI2.SPI_CLK: R72.2, TP41.1, U1.31 (RB10); also elsewhere on the board
/SPI2.SPI_MISO: R221.2, TP44.1; also elsewhere on the board
/SPI2.SPI_MOSI: R23.2, TP42.1; also elsewhere on the board
/SPI2.SPI_~CS: R214.1, TP43.1, U1.33 (RC8); also elsewhere on the board
GND: C1.1, C3.1, C4.1, C5.1, C6.1, C42.1, C43.1, C44.1, C45.1, C46.1, C47.1, C48.1, C49.1, C50.1, C51.1, C52.1, C53.1, C54.1, C55.1, C75.1, C85.1, C103.1, C253.1, D1.3 (VBUS), D1.6 (GND), D49.3 (GND), J10.3, Q21.2 (S), Q25.2 (S), Q26.2 (S), R8.1, R28.1, R64.1, R66.1, R68.1, R71.1, R72.1, R87.1, R114.1, S1.1, S2.1, U1.4 (VSS), U1.10 (AVSS), U1.18 (VSS), U1.25 (VSS), U1.39 (VSS), U1.47 (VSS), U1.59 (VSS), U1.65 (PAD), U20.2 (GND), Y3.2 (GND), Y3.4 (GND); also elsewhere on the board
unnamed: C3.2, R7.1, R8.2, R78.2
unnamed: C4.2, R63.1, R64.2, R77.2
unnamed: C6.2, R65.1, R66.2, R76.2
unnamed: C45.2, R67.1, R68.2, R75.2
unnamed: C51.2, R70.1, R71.2, R74.2
unnamed: D1.1 (I/O1), D7.1 (K), J10.1, S2.2
unnamed: D1.5 (I/O4), J10.4, U1.27 (ICSPDAT)
unnamed: D1.8 (I/O6), J10.5, U1.28 (ICSPCLK)
unnamed: D6.2 (A), D7.2 (A), R85.1, U1.64 (~MCLR)
unnamed: D10.2 (A), R133.2
unnamed: C103.2, Q21.1 (G), R30.1, R133.1
unnamed: Q25.3 (D), Q26.1 (G), R153.1
unnamed: Q26.3 (D), R22.2, R232.1
unnamed: C1.2, R1.1, U1.3 (RA1)
unnamed: R74.1, U1.12 (RA2)
unnamed: R75.1, U1.14 (RA4)
unnamed: R76.1, U1.15 (RA5)
unnamed: R77.1, U1.16 (RA6)
unnamed: R78.1, U1.2 (RA7)
unnamed: R79.1, U1.8 (RA9)
unnamed: R3.1, U1.9 (RA10)
unnamed: C46.2, R5.1, U1.20 (RB0)
unnamed: R80.1, U1.21 (RB1*)
unnamed: R81.1, U1.22 (RB2)
unnamed: C42.2, R6.1, U1.17 (RB5)
unnamed: R82.1, U1.29 (RB6)
unnamed: R84.1, U1.23 (RB8)
unnamed: C253.2, R69.1, U1.24 (RB9)
unnamed: R23.1, U1.32 (RB11)
unnamed: R4.1, U1.41 (RC2)
unnamed: R219.1, U1.43 (RC3)
unnamed: R220.1, U1.35 (RC6)
unnamed: R221.1, U1.34 (RC9)
unnamed: R228.1, U1.46 (RC11)
unnamed: R226.1, U1.54 (RD3)
unnamed: R227.1, U1.61 (RD4)
unnamed: R86.1, U1.49 (RD9)
unnamed: R222.1, U1.62 (RD11)
unnamed: R223.1, U1.63 (RD12)
unnamed: C49.2, R73.1, U1.38 (OSC1), Y3.1 (XI)
unnamed: C48.2, R73.2, U1.37 (OSCO), Y3.3 (XO)
unnamed: C55.2, R22.1, U20.4 (WDI)
unnamed: R24.1, R28.2, U20.3 (~EN)

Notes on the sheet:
PIC MOSI to CMx MISO
PicKit 5 or better
CMx MOSI to PIC MISO
Resistors are 1% 1/16W 0402 unless otherwise noted Capacitors are 10% 50V X7R 0402 unless otherwise noted
~{EN} Power-up delay
